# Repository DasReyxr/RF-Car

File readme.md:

# RF-Car

A car
## Directory structure
```
├── design
│   ├── KicadDesign
│   │   ├── Design.kicad_pcb
│   │   ├── Design.kicad_pro
│   │   ├── Design.kicad_sch
│   └── Schematic.pdf
├── doc
│   ├── AC
│   ├── ConfigAC.tex
│   ├── Examen1.pdf
│   ├── Examen1.tex
│   └── Tarjeta didáctica de control para tiristores.pdf
├── README.md
├── src
│   └── render.png
├── sim
│   └── SCR.asc
```

- `SCRController.kicad_sch` / `.kicad_pcb` / `.kicad_pro` — KiCad design
- `SCRController.step` — 3D model
- `Tarjeta didáctica de control para tiristores.pdf` — design writeup
- `simulation.asc.txt` — LTspice simulation

**Photos of the built board — coming soon**

## Files

## Credit
Built as coursework with [DasReyxr](https://github.com/DasReyxr)  and [Kevin Lara](https://github.com/Gyonyu) — original project history in [DasReyxr/HW-Projects](https://github.com/DasReyxr/HW-Projects). This copy is curated separately with a proper writeup and renders.

## Template
```
mkdir code design doc scripts sim src
```

```
tree >> README.md
```

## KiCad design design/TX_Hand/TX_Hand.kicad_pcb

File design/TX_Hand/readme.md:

# Log File
## 6-29-26

## 6-29-26

## 6-29-26

## 6-24-26

## 6-23-26

# 8-27-26

# 10-10-26
- Changed footprints
- Attempt to do it in one layer
- Unconnected VCC and RF mod

# 10- 11-26
- Autoroute best try (Still not working)
- VCC, SW_Luz and GND not connectedº

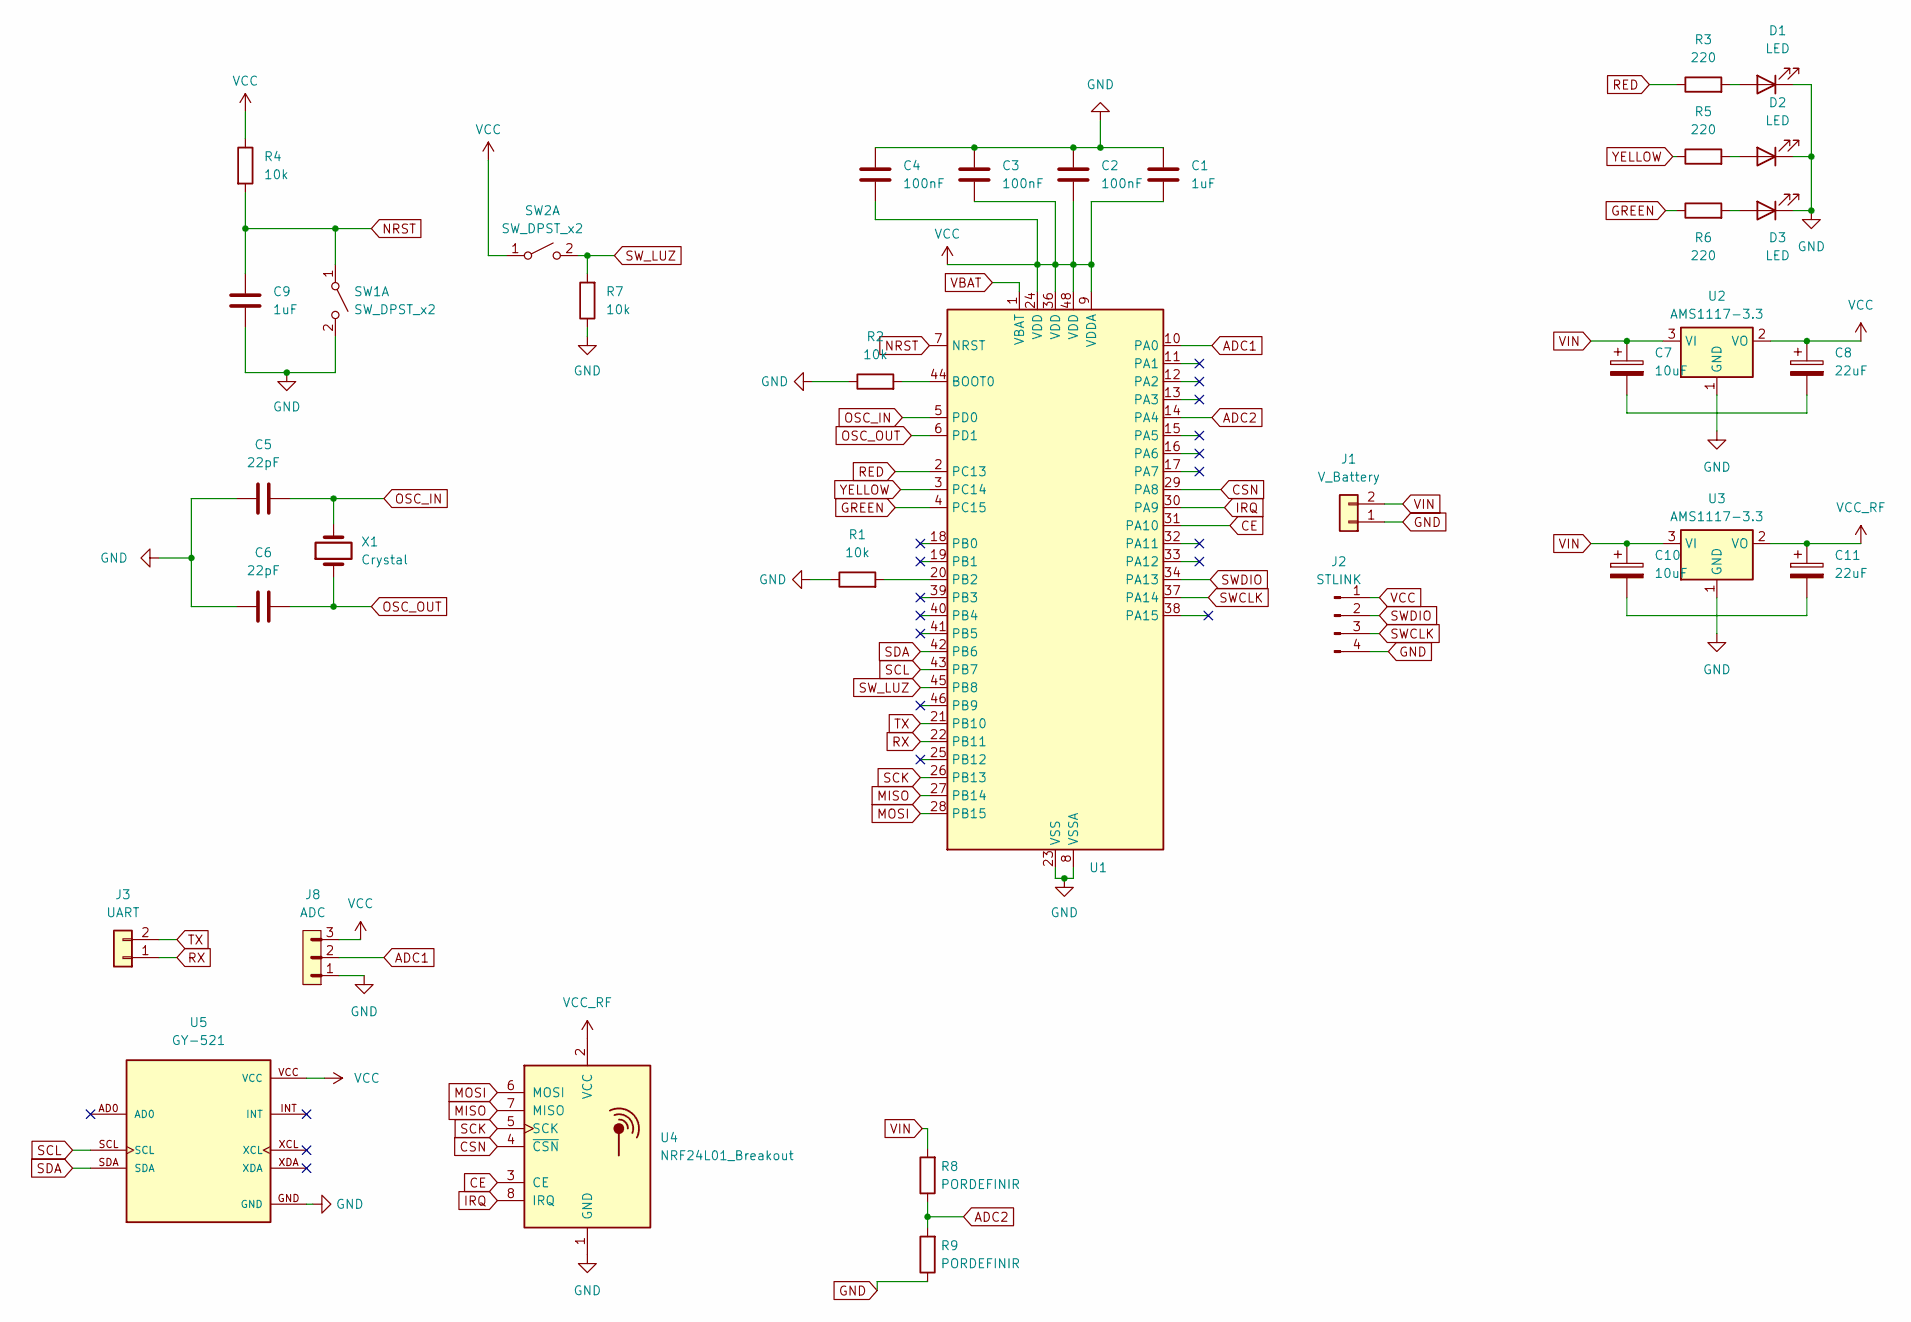
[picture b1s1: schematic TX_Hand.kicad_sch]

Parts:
C1, C9: 1uF; C_0805_2012Metric_Pad1.18x1.45mm_HandSolder
C2, C3, C4: 100nF; C_0805_2012Metric_Pad1.18x1.45mm_HandSolder
C5, C6: 22pF; C_0805_2012Metric_Pad1.18x1.45mm_HandSolder
C7, C10: 10uF; C_0805_2012Metric_Pad1.18x1.45mm_HandSolder
C8, C11: 22uF; C_0805_2012Metric_Pad1.18x1.45mm_HandSolder
D1, D2, D3: LED; LED_0805_2012Metric
J1: V_Battery; PinHeader_1x02_P2.54mm_Vertical
J2: STLINK; PinHeader_1x04_P2.54mm_Vertical
J3: UART; PinHeader_1x02_P2.54mm_Vertical
J8: ADC; PinHeader_1x03_P2.54mm_Vertical
R1, R2, R4, R7: 10k; R_0805_2012Metric
R3, R5, R6: 220; R_0805_2012Metric
R8, R9: PORDEFINIR; R_0805_2012Metric
SW1: SW_DPST_x2; SW_Push_1P1T_NO_E-Switch_TL3301NxxxxxG
SW2: SW_DPST_x2; PinHeader_1x02_P2.54mm_Vertical
U1: STM32F103C8Tx; LQFP-48_7x7mm_P0.5mm
U2, U3: AMS1117-3.3; SOT-223-3_TabPin2
U4: NRF24L01_Breakout; nRF24L01_Breakout
U5: GY-521; MODULE_GY-521; PARTREV NA
X1: Crystal; XTAL_NX5032_NDK

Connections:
ADC1: J8.2, U1.10 (PA0)
ADC2: R8.1, R9.2, U1.14 (PA4)
CE: U1.31 (PA10), U4.3 (CE)
CSN: U1.29 (PA8), U4.4 (~CSN)
GND: C1.2, C2.2, C3.2, C4.2, C5.2, C6.2, C9.1, D1.1 (K), D2.1 (K), D3.1 (K), J1.1, J2.4, J8.1, R1.1, R2.1, R7.1, R9.1, SW1.2 (B), U1.8 (VSSA), U1.23 (VSS), U1.35 (VSS), U1.47 (VSS), U2.1 (GND), U3.1 (GND), U4.1 (GND), U5.GND
GREEN: R6.1, U1.4 (PC15)
IRQ: U1.30 (PA9), U4.8 (IRQ)
MISO: U1.27 (PB14), U4.7 (MISO)
MOSI: U1.28 (PB15), U4.6 (MOSI)
NRST: C9.2, R4.2, SW1.1 (A), U1.7 (NRST)
unnamed: C7.2, C8.2
unnamed: C10.2, C11.2
unnamed: D1.2 (A), R3.2
unnamed: D2.2 (A), R5.2
unnamed: D3.2 (A), R6.2
unnamed: R2.2, U1.44 (BOOT0)
unnamed: R1.2, U1.20 (PB2)
OSC_IN: C5.1, U1.5 (PD0), X1.2
OSC_OUT: C6.1, U1.6 (PD1), X1.1
RED: R3.1, U1.2 (PC13)
RX: J3.1, U1.22 (PB11)
SCK: U1.26 (PB13), U4.5 (SCK)
SCL: U1.43 (PB7), U5.SCL
SDA: U1.42 (PB6), U5.SDA
SWCLK: J2.3, U1.37 (PA14)
SWDIO: J2.2, U1.34 (PA13)
SW_LUZ: R7.2, SW2.2 (B), U1.45 (PB8)
TX: J3.2, U1.21 (PB10)
VBAT: U1.1 (VBAT)
VCC: C1.1, C2.1, C3.1, C4.1, C8.1, J2.1, J8.3, R4.1, SW2.1 (A), U1.9 (VDDA), U1.24 (VDD), U1.36 (VDD), U1.48 (VDD), U2.2 (VO), U5.VCC
VCC_RF: C11.1, U3.2 (VO), U4.2 (VCC)
VIN: C7.1, C10.1, J1.2, R8.2, U2.3 (VI), U3.3 (VI)
YELLOW: R5.1, U1.3 (PC14)

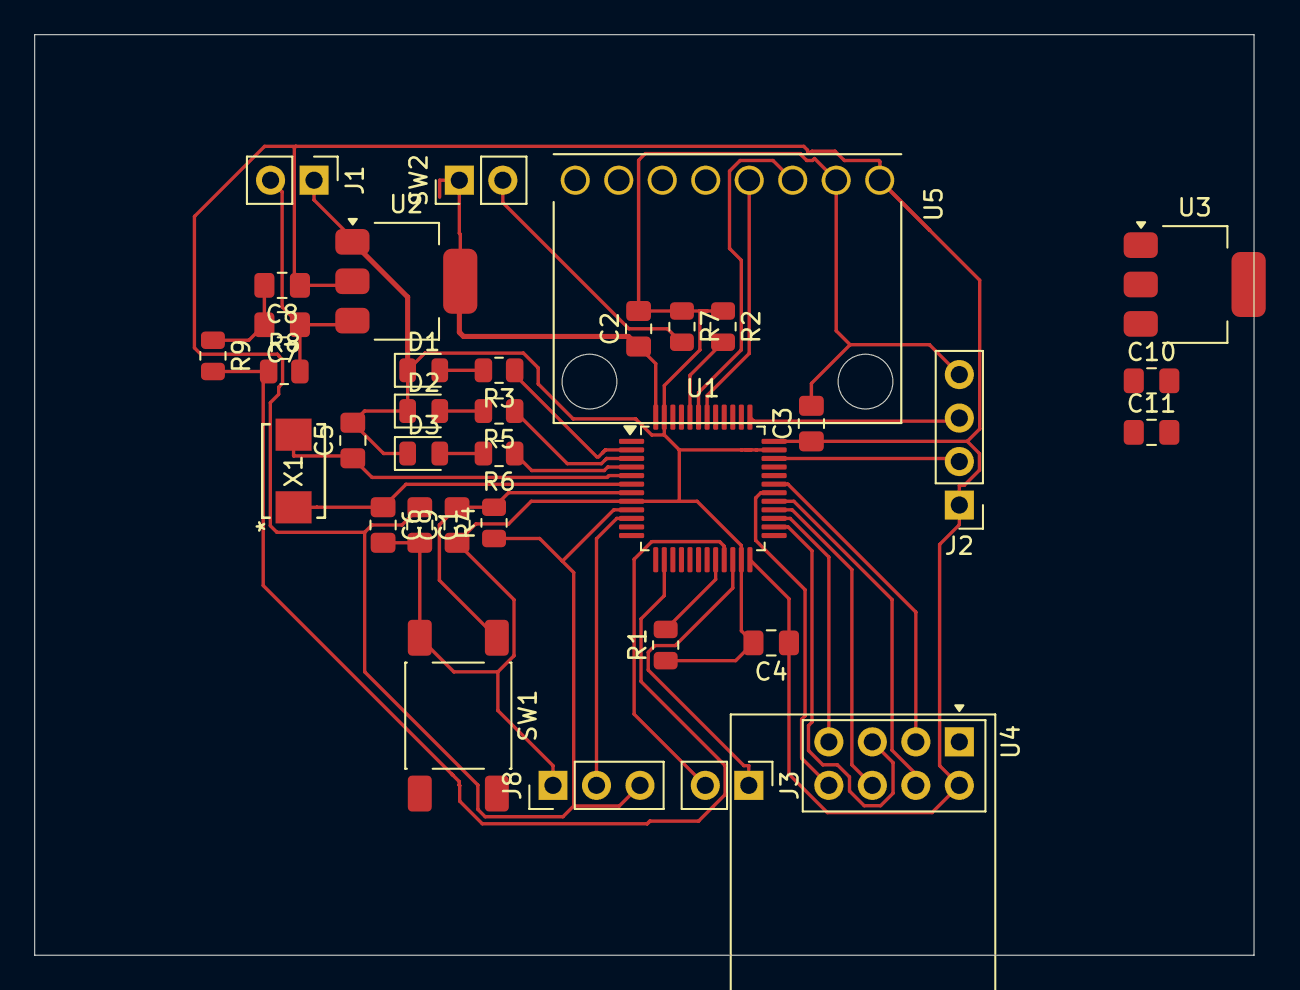
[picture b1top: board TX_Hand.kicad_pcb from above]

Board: 2 copper layers, 71.2 x 53.8 mm, 35 parts (0 on the bottom side), 32 nets.

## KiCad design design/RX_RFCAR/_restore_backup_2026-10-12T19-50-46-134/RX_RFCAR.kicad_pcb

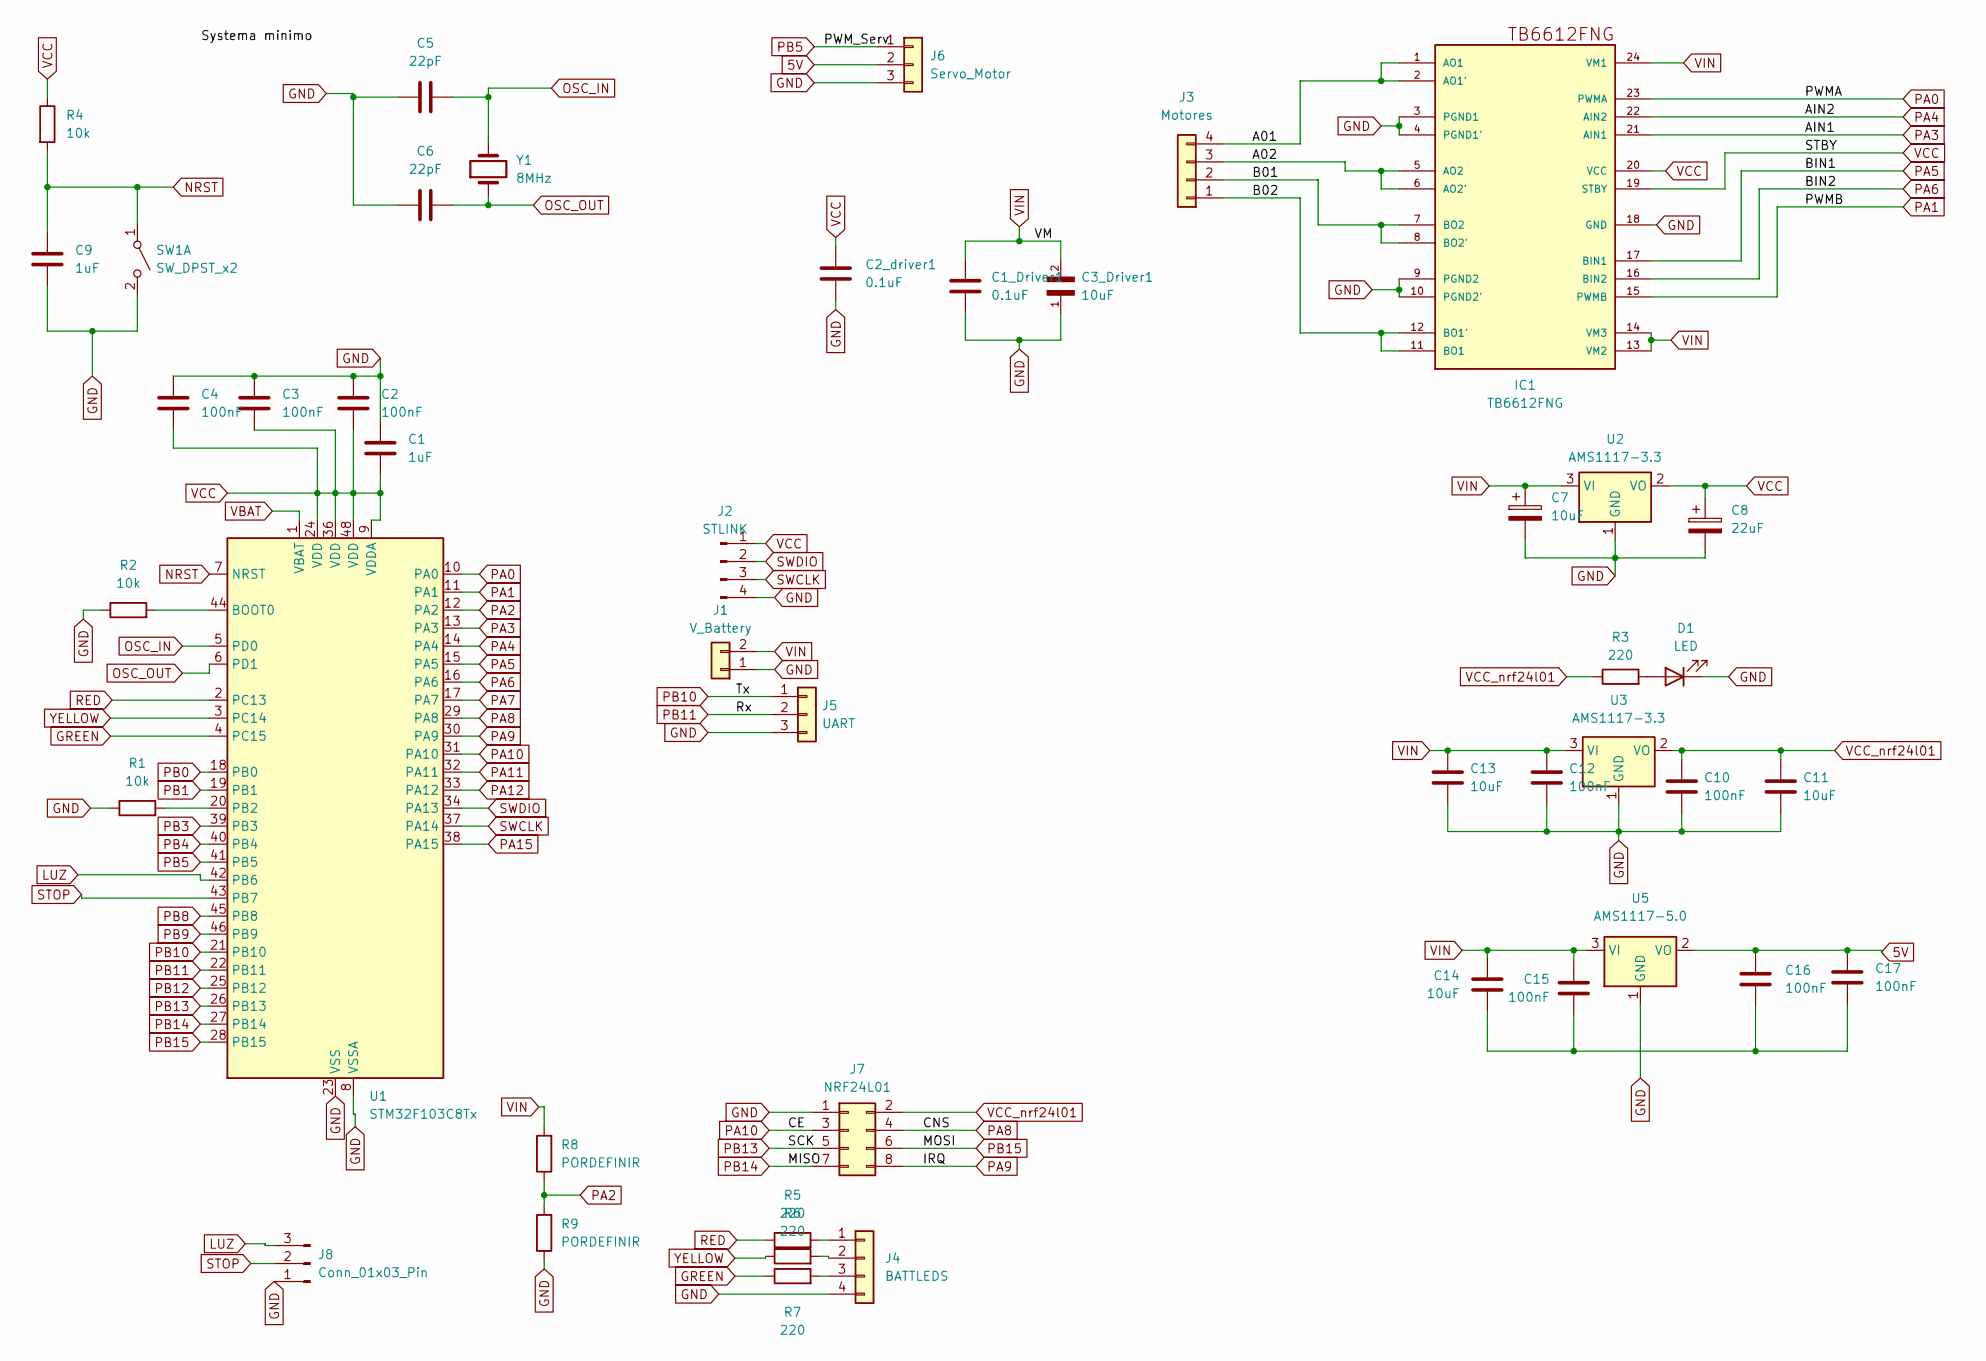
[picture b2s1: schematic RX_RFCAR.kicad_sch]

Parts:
C1: 1uF; C_0805_2012Metric
C1_Driver1, C2_driver1: 0.1uF; C_0805_2012Metric
C2, C3, C4, C10, C12, C15, C16, C17: 100nF; C_0805_2012Metric_Pad1.18x1.45mm_HandSolder
C3_Driver1: 10uF; CAPPC3528X210N; DigiKey_Part_Number 478-1682-1-ND
C5, C6: 22pF; C_0805_2012Metric_Pad1.18x1.45mm_HandSolder
C7, C11, C13, C14: 10uF; C_0805_2012Metric_Pad1.18x1.45mm_HandSolder
C8: 22uF; C_0805_2012Metric_Pad1.18x1.45mm_HandSolder
C9: 1uF; C_0805_2012Metric_Pad1.18x1.45mm_HandSolder
D1: LED; LED_0603_1608Metric
IC1: TB6612FNG; SSOP-24_5.3x8.2mm_P0.65mm
J1: V_Battery; PinHeader_1x02_P2.54mm_Vertical
J2: STLINK; PinHeader_1x04_P2.54mm_Vertical
J3: Motores; PinHeader_1x04_P2.54mm_Vertical
J4: BATTLEDS; PinHeader_1x04_P2.54mm_Vertical
J5: UART; PinHeader_1x03_P2.54mm_Vertical
J6: Servo_Motor; PinHeader_1x03_P2.54mm_Vertical
J7: NRF24L01; PinHeader_2x04_P2.54mm_Vertical
J8: Conn_01x03_Pin; PinHeader_1x03_P2.54mm_Vertical
R1, R2, R4: 10k; R_0805_2012Metric
R3, R5, R6, R7: 220; R_0805_2012Metric
R8, R9: PORDEFINIR; R_0805_2012Metric
SW1: SW_DPST_x2; SW_Push_1P1T_NO_E-Switch_TL3301NxxxxxG
U1: STM32F103C8Tx; LQFP-48_7x7mm_P0.5mm
U2, U3: AMS1117-3.3; SOT-223-3_TabPin2
U5: AMS1117-5.0; SOT-223-3_TabPin2
Y1: 8MHz; XTAL_NX5032_NDK

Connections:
5V: C16.1, C17.1, J6.2, U5.2 (VO)
/A01: IC1.1 (AO1), IC1.2 (AO1'), J3.4
/A02: IC1.5 (AO2), IC1.6 (AO2'), J3.3
/B01: IC1.7 (BO2), IC1.8 (BO2'), J3.2
/B02: IC1.11 (BO1), IC1.12 (BO1'), J3.1
GREEN: R7.1, U1.4 (PC15)
LUZ: J8.3, U1.42 (PB6)
NRST: C9.2, R4.2, SW1.1 (A), U1.7 (NRST)
unnamed: D1.2 (A), R3.2
unnamed: J4.1, R5.2
unnamed: J4.2, R6.2
unnamed: J4.3, R7.2
unnamed: R2.2, U1.44 (BOOT0)
unnamed: R1.2, U1.20 (PB2)
OSC_IN: C5.1, U1.5 (PD0), Y1.2
OSC_OUT: C6.1, U1.6 (PD1), Y1.1
PA0: IC1.23 (PWMA), U1.10 (PA0)
PA1: IC1.15 (PWMB), U1.11 (PA1)
PA2: R8.1, R9.2, U1.12 (PA2)
PA3: IC1.21 (AIN1), U1.13 (PA3)
PA4: IC1.22 (AIN2), U1.14 (PA4)
PA5: IC1.17 (BIN1), U1.15 (PA5)
PA6: IC1.16 (BIN2), U1.16 (PA6)
PA7: U1.17 (PA7)
PA8: J7.4, U1.29 (PA8)
PA9: J7.8, U1.30 (PA9)
PA10: J7.3, U1.31 (PA10)
PA11: U1.32 (PA11)
PA12: U1.33 (PA12)
PA15: U1.38 (PA15)
PB0: U1.18 (PB0)
PB1: U1.19 (PB1)
PB3: U1.39 (PB3)
PB4: U1.40 (PB4)
PB5: J6.1, U1.41 (PB5)
PB8: U1.45 (PB8)
PB9: U1.46 (PB9)
PB10: J5.1, U1.21 (PB10)
PB11: J5.2, U1.22 (PB11)
PB12: U1.25 (PB12)
PB13: J7.5, U1.26 (PB13)
PB14: J7.7, U1.27 (PB14)
PB15: J7.6, U1.28 (PB15)
RED: R5.1, U1.2 (PC13)
STOP: J8.2, U1.43 (PB7)
SWCLK: J2.3, U1.37 (PA14)
SWDIO: J2.2, U1.34 (PA13)
VBAT: U1.1 (VBAT)
VCC: C1.1, C2.1, C2_driver1.1, C3.1, C4.1, C8.1, IC1.19 (STBY), IC1.20 (VCC), J2.1, R4.1, U1.9 (VDDA), U1.24 (VDD), U1.36 (VDD), U1.48 (VDD), U2.2 (VO)
VCC_nrf24l01: C10.1, C11.1, J7.2, R3.1, U3.2 (VO)
VIN: C1_Driver1.1, C3_Driver1.2, C7.1, C12.1, C13.1, C14.1, C15.1, IC1.13 (VM2), IC1.14 (VM3), IC1.24 (VM1), J1.2, R8.2, U2.3 (VI), U3.3 (VI), U5.3 (VI)
YELLOW: R6.1, U1.3 (PC14)

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
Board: 2 copper layers, 45 parts (0 on the bottom side), 41 nets, no tracks yet.

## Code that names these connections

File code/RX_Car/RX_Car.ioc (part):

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Mcu.Name=STM32F103C(8-B)Tx
Mcu.Package=LQFP48
Mcu.UserName=STM32F103C8Tx
PA0-WKUP.Signal=S_TIM2_CH1_ETR
PA1.Signal=S_TIM2_CH2
PA10.GPIOParameters=GPIO_Speed,GPIO_Label
PA10.GPIO_Label=CE
PA10.GPIO_Speed=GPIO_SPEED_FREQ_HIGH
PA10.Signal=GPIO_Output
PA13.Mode=Serial_Wire
PA13.Signal=SYS_JTMS-SWDIO
PA14.Mode=Serial_Wire
PA14.Signal=SYS_JTCK-SWCLK
PA2.Signal=ADCx_IN2
PA3.GPIOParameters=GPIO_Speed,GPIO_Label
PA3.GPIO_Label=LeftFront
PA3.GPIO_Speed=GPIO_SPEED_FREQ_HIGH
PA3.Signal=GPIO_Output
PA4.GPIOParameters=GPIO_Speed,GPIO_Label
PA4.GPIO_Label=LeftBack
PA4.GPIO_Speed=GPIO_SPEED_FREQ_HIGH
PA4.Signal=GPIO_Output
PA5.GPIOParameters=GPIO_Speed,GPIO_Label
PA5.GPIO_Label=RightFront
PA5.GPIO_Speed=GPIO_SPEED_FREQ_HIGH
PA5.Signal=GPIO_Output
PA6.GPIOParameters=GPIO_Speed,GPIO_Label
PA6.GPIO_Label=RightBack
PA6.GPIO_Speed=GPIO_SPEED_FREQ_HIGH
PA6.Signal=GPIO_Output
PA8.GPIOParameters=GPIO_Speed,GPIO_Label
PA8.GPIO_Label=CSN
PA8.GPIO_Speed=GPIO_SPEED_FREQ_HIGH
PA8.Signal=GPIO_Output
PA9.GPIOParameters=GPIO_Label,GPIO_ModeDefaultEXTI
PA9.GPIO_Label=IRQ
PA9.GPIO_ModeDefaultEXTI=GPIO_MODE_IT_FALLING
PA9.Signal=GPXTI9
PB0.GPIOParameters=GPIO_Label
PB0.GPIO_Label=LED_DIR1
PB0.Signal=GPIO_Output
PB1.GPIOParameters=GPIO_Label
PB1.GPIO_Label=LED_DIR2
PB1.Signal=GPIO_Output
PB10.Mode=Asynchronous
PB10.Signal=USART3_TX
PB11.Mode=Asynchronous
PB11.Signal=USART3_RX
PB13.Mode=Full_Duplex_Master
PB13.Signal=SPI2_SCK
PB14.Mode=Full_Duplex_Master
PB14.Signal=SPI2_MISO
PB15.Mode=Full_Duplex_Master
PB15.Signal=SPI2_MOSI
PB5.Signal=S_TIM3_CH2
PB6.GPIOParameters=GPIO_Label
PB6.GPIO_Label=LUZ
PB6.Signal=GPIO_Output
PB7.GPIOParameters=GPIO_Label
PB7.GPIO_Label=STOP
PB7.Signal=GPIO_Output
PC13-TAMPER-RTC.GPIOParameters=GPIO_Label
PC13-TAMPER-RTC.GPIO_Label=RED
PC13-TAMPER-RTC.Signal=GPIO_Output
PC14-OSC32_IN.GPIOParameters=GPIO_Label
PC14-OSC32_IN.GPIO_Label=YELLOW
PC14-OSC32_IN.Signal=GPIO_Output
PC15-OSC32_OUT.GPIOParameters=GPIO_Label
PC15-OSC32_OUT.GPIO_Label=GREEN
PC15-OSC32_OUT.Signal=GPIO_Output
PD0-OSC_IN.Mode=HSE-External-Oscillator
PD0-OSC_IN.Signal=RCC_OSC_IN
PD1-OSC_OUT.Mode=HSE-External-Oscillator
PD1-OSC_OUT.Signal=RCC_OSC_OUT
RCC.SYSCLKFreq_VALUE=16000000
RCC.SYSCLKSource=RCC_SYSCLKSOURCE_PLLCLK
board=custom
